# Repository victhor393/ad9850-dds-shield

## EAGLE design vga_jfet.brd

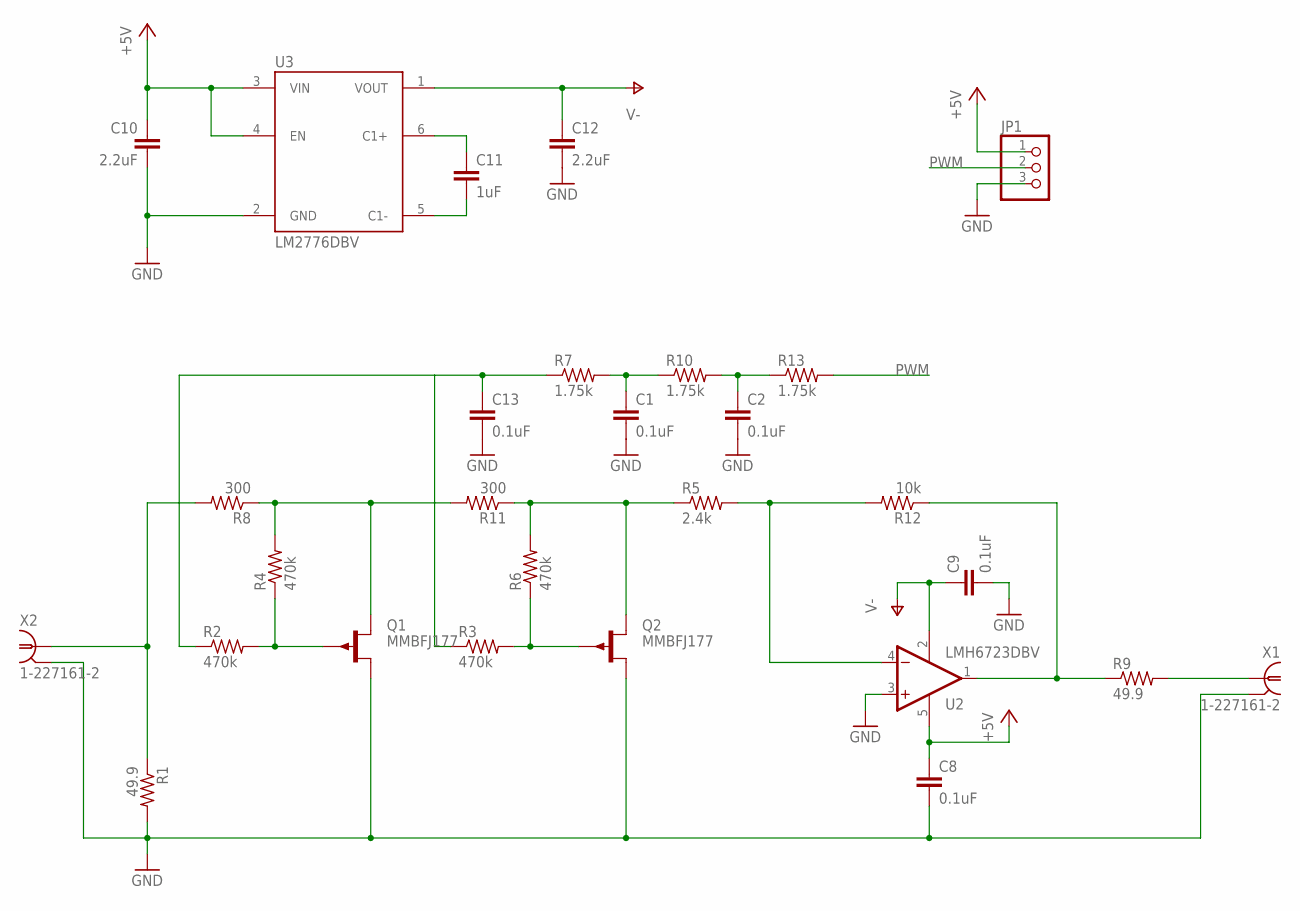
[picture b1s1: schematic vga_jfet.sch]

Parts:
C1, C2, C8, C9, C13: 0.1uF; C0603
C10, C12: 2.2uF; C0603
C11: 1uF; C0603
JP1: PINHD-1X3; 1X03
Q1, Q2: MMBFJ177; SOT23
R1, R9: 49.9; R0603
R2, R3, R4, R6: 470k; R0603
R5: 2.4k; R0603
R7, R10, R13: 1.75k; R0603
R8, R11: 300; R0603
R12: 10k; R0603
U2: LMH6723DBV; SOT23-DBV
U3: LM2776DBV; SOT23-6
X1, X2: 1-227161-2; AMP_227161

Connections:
+5V: C8.1, C10.1, JP1.1, U2.5 (V+), U3.3 (VIN), U3.4 (EN)
GND: C1.2, C2.2, C8.2, C9.2, C10.2, C12.2, C13.2, JP1.3, Q1.1 (D), Q2.1 (D), R1.2, U2.3 (+IN), U3.2 (GND), X1.2, X2.2
unnamed: C1.1, R7.2, R10.1
unnamed: Q2.3 (G), R3.2, R6.1
unnamed: C2.1, R10.2, R13.1
unnamed: Q1.3 (G), R2.2, R4.1
unnamed: C13.1, R2.1, R3.1, R7.1
unnamed: R5.2, R12.2, U2.4 (-IN)
unnamed: R1.1, R8.2, X2.1
unnamed: Q2.2 (S), R5.1, R6.2, R11.1
unnamed: Q1.2 (S), R4.2, R8.1, R11.2
unnamed: R9.1, R12.1, U2.1 (OUT)
unnamed: R9.2, X1.1
unnamed: C11.1, U3.6 (C1+)
unnamed: C11.2, U3.5 (C1-)
PWM: JP1.2, R13.2
V-: C9.1, C12.1, U2.2 (V-), U3.1 (VOUT)

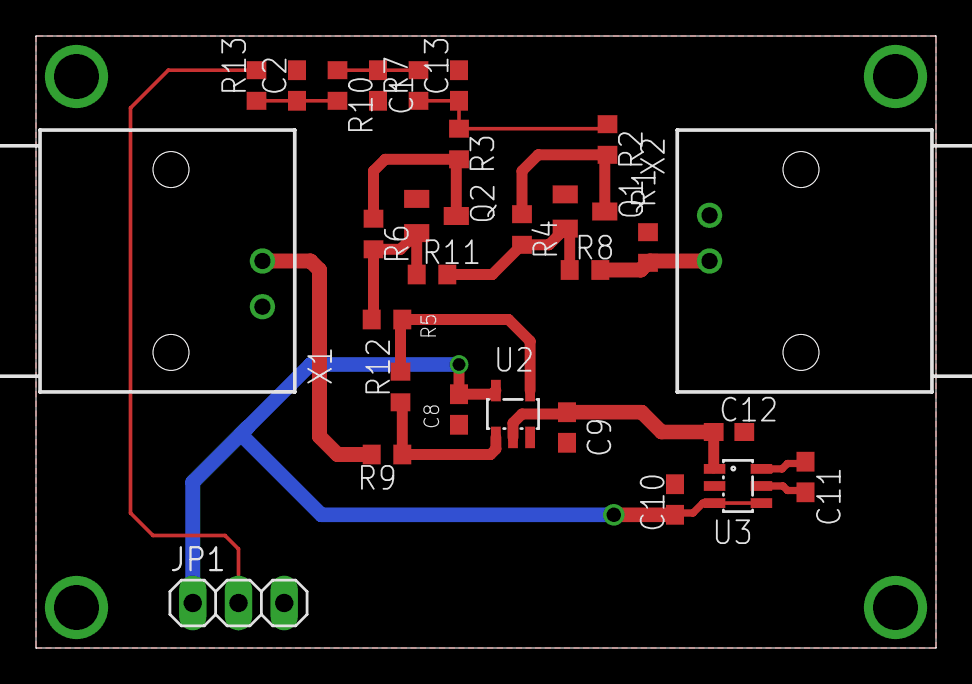
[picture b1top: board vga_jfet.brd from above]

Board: 2 copper layers, 50.0 x 34.0 mm, 28 parts (0 on the bottom side), 17 nets.

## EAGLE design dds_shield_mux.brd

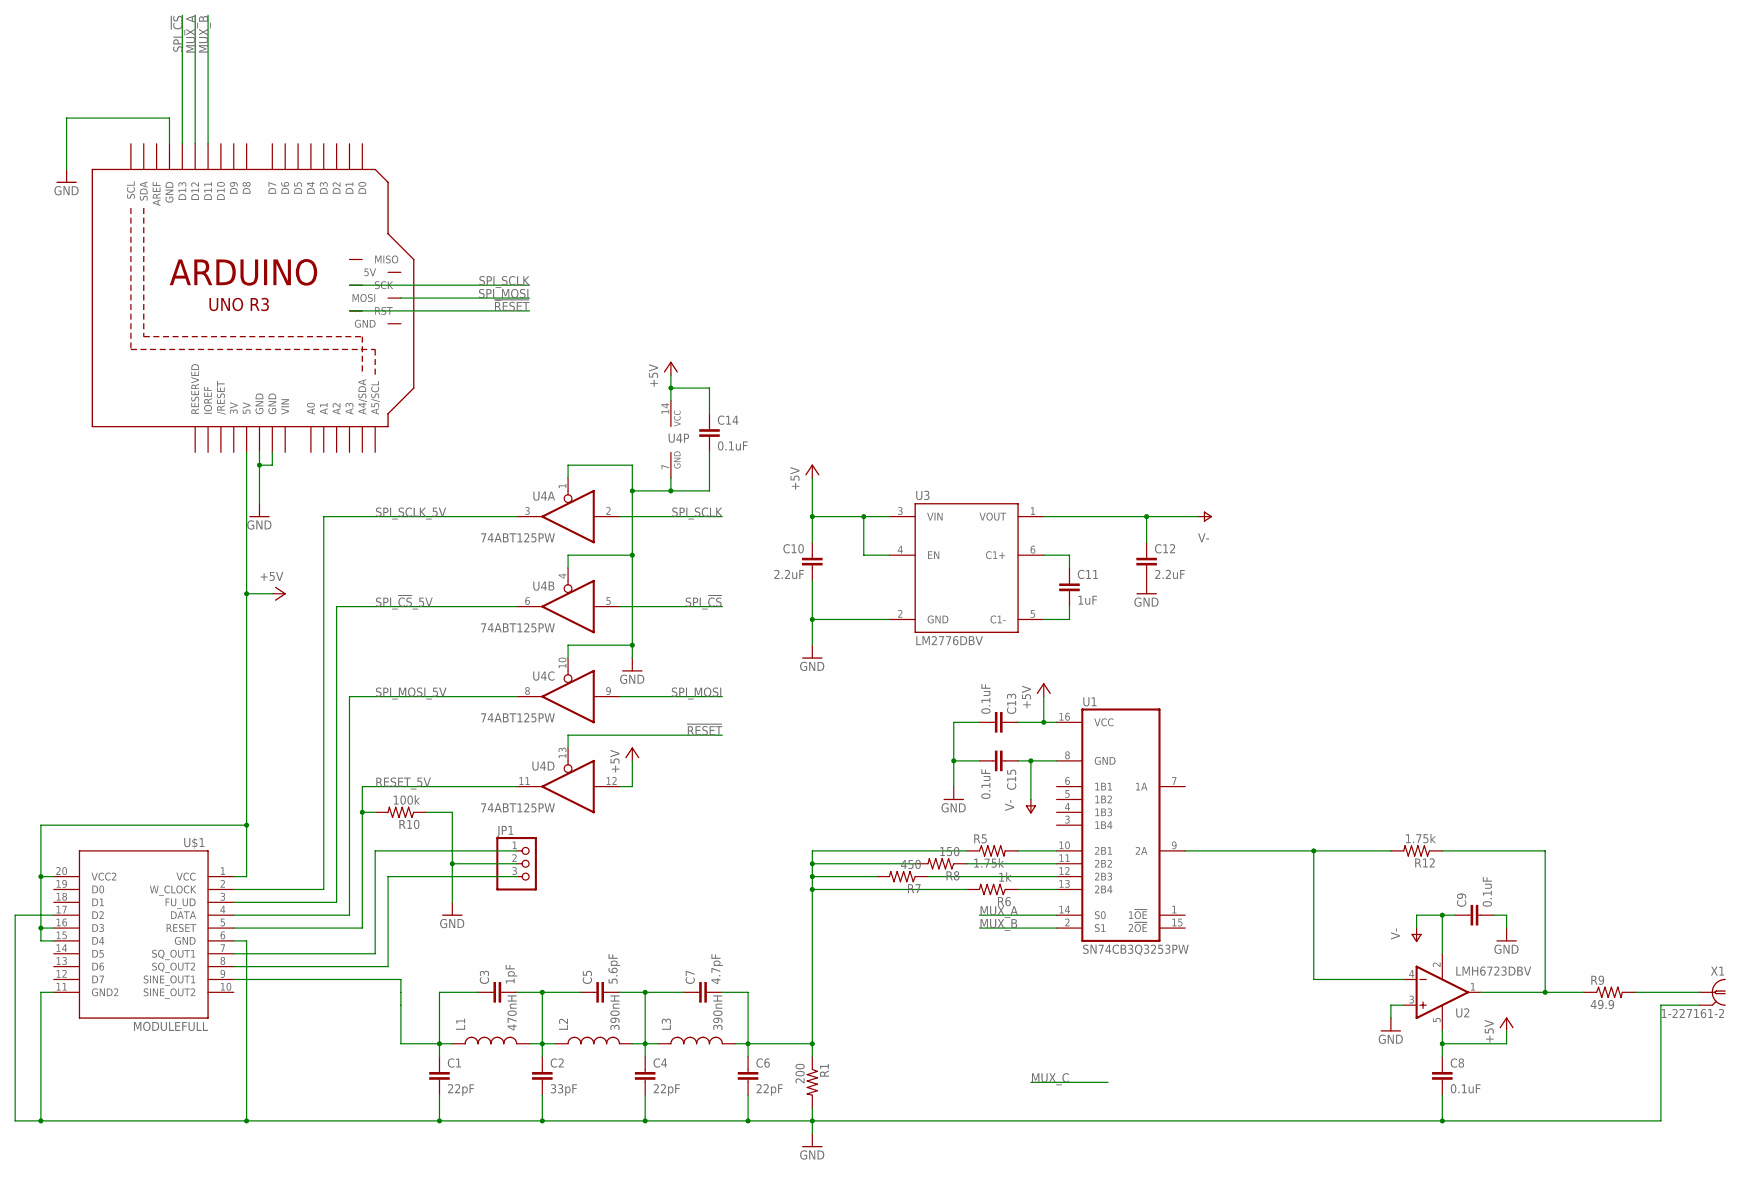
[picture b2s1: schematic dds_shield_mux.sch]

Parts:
C1, C4, C6: 22pF; C0603
C2: 33pF; C0603
C3: 1pF; C0603
C5: 5.6pF; C0603
C7: 4.7pF; C0603
C8, C9, C13, C14, C15: 0.1uF; C0603
C10, C12: 2.2uF; C0603
C11: 1uF; C0603
JP1: PINHD-1X3/90; 1X03/90
L1: 470nH; 0603
L2, L3: 390nH; 0603
M1: ARDUINO_R3_ICSP; ARDUINOR3_ICSP
R1: 200; R0603
R5, R12: 1.75k; R0603
R6: 1k; R0603
R7: 450; R0603
R8: 150; R0603
R9: 49.9; R0603
R10: 100k; R0603
U1: SN74CB3Q3253PW; PW_R-PDSO-G16
U2: LMH6723DBV; SOT23-DBV
U3: LM2776DBV; SOT23-6
U4: 74ABT125PW; TSSOP14
U$1: MODULEFULL; MODULE
X1: 1-227161-2; AMP_227161

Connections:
3V: M1.3V
!RESET: M1.RESET_ICSP (RST), U4.13 (OE)
+5V: C8.1, C10.1, C13.1, C14.1, M1.5V, U1.16 (VCC), U2.5 (V+), U3.3 (VIN), U3.4 (EN), U4.12 (I), U4.14 (VCC), U$1.1 (VCC), U$1.15 (D4), U$1.16 (D3), U$1.20 (VCC2)
GND: C1.2, C2.2, C4.2, C6.2, C8.2, C9.2, C10.2, C12.2, C13.2, C14.2, C15.2, JP1.2, M1.GND, M1.GND@1 (GND), M1.GND@3 (GND), R1.2, R10.1, U2.3 (+IN), U3.2 (GND), U4.1 (OE), U4.4 (OE), U4.7 (GND), U4.10 (OE), U$1.6 (GND), U$1.11 (GND2), U$1.17 (D2), X1.2
MUX_A: M1.D12, U1.14 (S0)
MUX_B: M1.D11, U1.2 (S1)
unnamed: C1.1, C3.1, L1.1, U$1.9 (SINE_OUT1)
unnamed: R8.1, U1.11 (2B2)
unnamed: C2.1, C3.2, C5.1, L1.2, L2.1
unnamed: C4.1, C5.2, C7.1, L2.2, L3.1
unnamed: R5.2, U1.10 (2B1)
unnamed: R7.1, U1.12 (2B3)
unnamed: R12.2, U1.9 (2A), U2.4 (-IN)
unnamed: R6.1, U1.13 (2B4)
unnamed: C6.1, C7.2, L3.2, R1.1, R5.1, R6.2, R7.2, R8.2
unnamed: R9.1, R12.1, U2.1 (OUT)
unnamed: R9.2, X1.1
unnamed: JP1.1, U$1.7 (SQ_OUT1)
unnamed: C11.1, U3.6 (C1+)
unnamed: C11.2, U3.5 (C1-)
unnamed: JP1.3, U$1.8 (SQ_OUT2)
RESET_5V: R10.2, U4.11 (O), U$1.5 (RESET)
SPI_!CS: M1.D13, U4.5 (I)
SPI_!CS!_5V: U4.6 (O), U$1.3 (FU_UD)
SPI_MOSI: M1.MOSI, U4.9 (I)
SPI_MOSI_5V: U4.8 (O), U$1.4 (DATA)
SPI_SCLK: M1.SCK, U4.2 (I)
SPI_SCLK_5V: U4.3 (O), U$1.2 (W_CLOCK)
V-: C9.1, C12.1, C15.1, U1.8 (GND), U2.2 (V-), U3.1 (VOUT)
VIN: M1.VIN

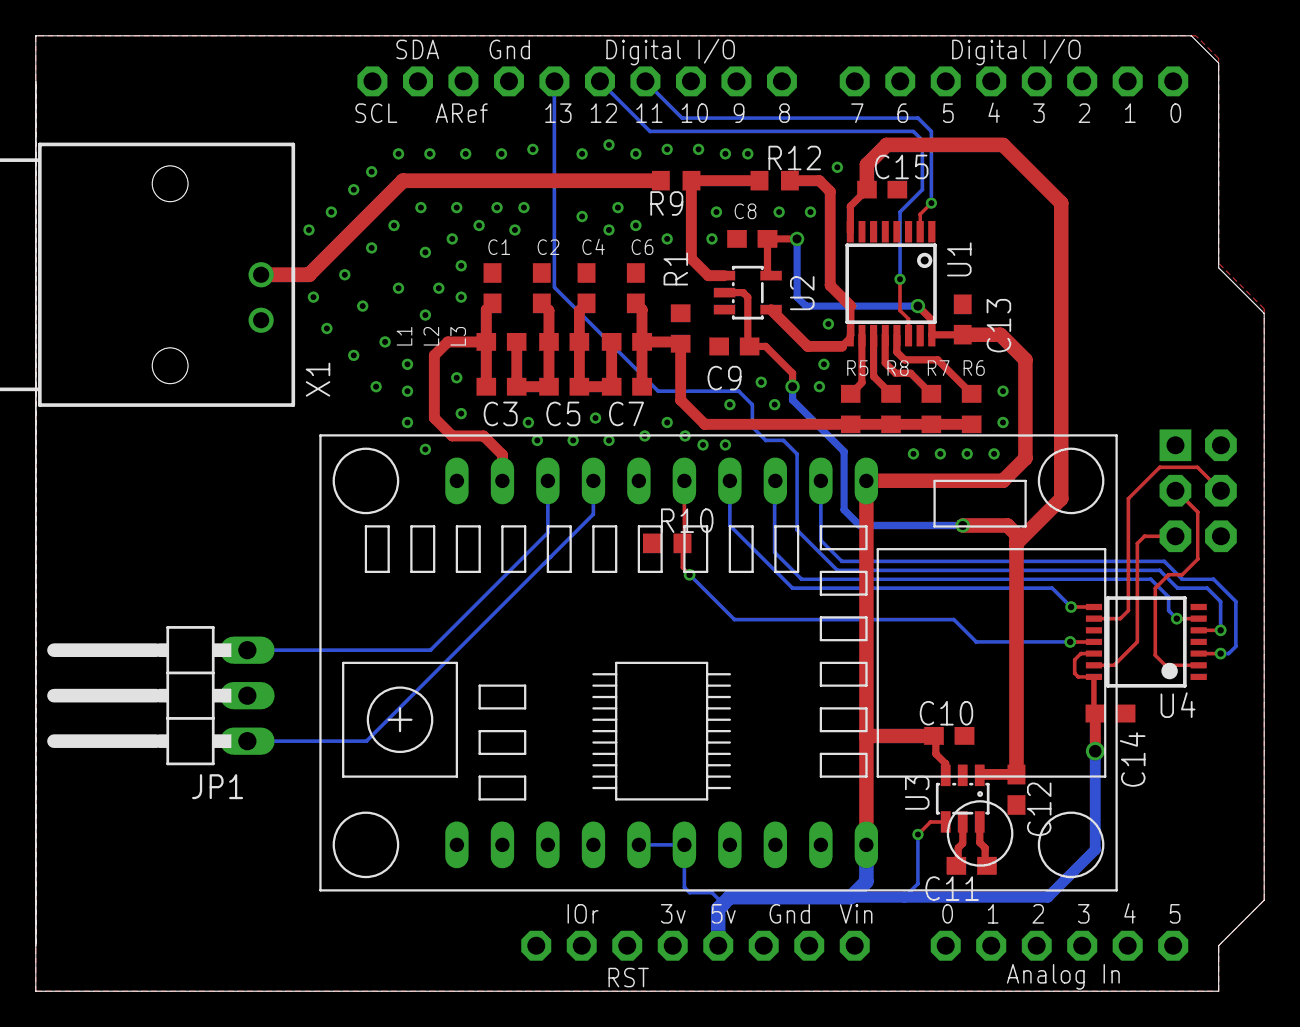
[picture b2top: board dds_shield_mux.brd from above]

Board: 2 copper layers, 68.6 x 53.3 mm, 34 parts (0 on the bottom side), 28 nets.

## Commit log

2019-05-21 Added schematic and board layout in pdf format

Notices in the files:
parts and their libraries:
SparkFun: Licensing: CC v3.0 Share-Alike You are welcome to use this library for commercial purposes.
